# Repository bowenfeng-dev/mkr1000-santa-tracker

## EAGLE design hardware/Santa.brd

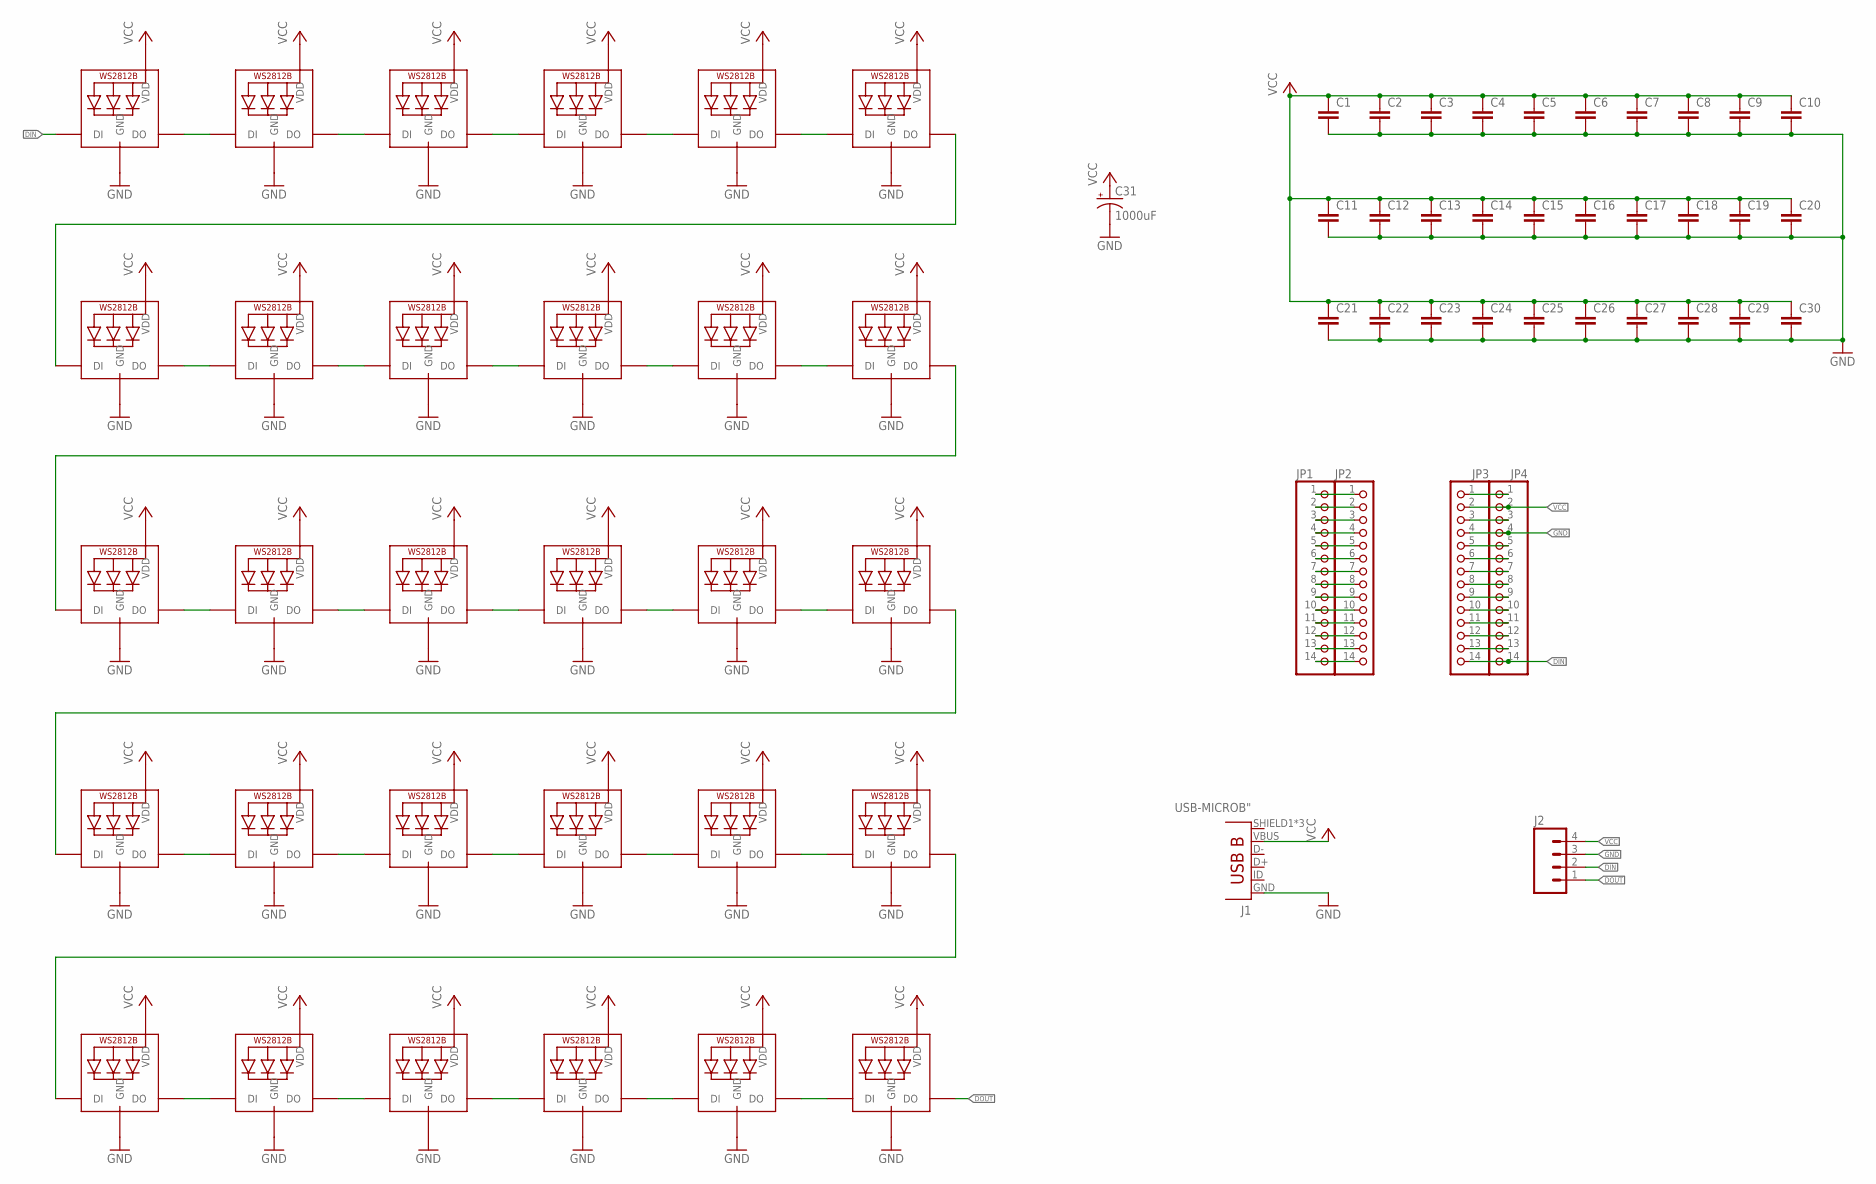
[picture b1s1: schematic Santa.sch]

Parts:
C1, C2, C3, C4, C5, C6, C7, C8, C9, C10, C11, C12, C13, C14, C15, C16, C17, C18, C19, C20, C21, C22, C23, C24, C25, C26, C27, C28, C29, C30: CC0603; C0603
C31: 1000uF; SMC_C
J1: USB-MICROB"; USB-B-MICRO-SMD_V03
J2: M04LOCK_LONGPADS; 1X04_LOCK_LONGPADS
JP1, JP2, JP3, JP4: PINHD-1X14-CB; 1X14-CB
LED1, LED2, LED3, LED4, LED5, LED6, LED7, LED8, LED9, LED10, LED11, LED12, LED13, LED14, LED15, LED16, LED17, LED18, LED19, LED20, LED21, LED22, LED23, LED24, LED25, LED26, LED27, LED28, LED29, LED30: WS2812B5050; WS2812B

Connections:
DIN: J2.2, JP3.14, JP4.14, LED1.4-DIN (DI)
DOUT: J2.1, LED30.2-DOUT (DO)
GND: C1.2, C2.2, C3.2, C4.2, C5.2, C6.2, C7.2, C8.2, C9.2, C10.2, C11.2, C12.2, C13.2, C14.2, C15.2, C16.2, C17.2, C18.2, C19.2, C20.2, C21.2, C22.2, C23.2, C24.2, C25.2, C26.2, C27.2, C28.2, C29.2, C30.2, C31.-, J1.GND, J2.3, JP3.4, JP4.4, LED1.3-GND (GND), LED2.3-GND (GND), LED3.3-GND (GND), LED4.3-GND (GND), LED5.3-GND (GND), LED6.3-GND (GND), LED7.3-GND (GND), LED8.3-GND (GND), LED9.3-GND (GND), LED10.3-GND (GND), LED11.3-GND (GND), LED12.3-GND (GND), LED13.3-GND (GND), LED14.3-GND (GND), LED15.3-GND (GND), LED16.3-GND (GND), LED17.3-GND (GND), LED18.3-GND (GND), LED19.3-GND (GND), LED20.3-GND (GND), LED21.3-GND (GND), LED22.3-GND (GND), LED23.3-GND (GND), LED24.3-GND (GND), LED25.3-GND (GND), LED26.3-GND (GND), LED27.3-GND (GND), LED28.3-GND (GND), LED29.3-GND (GND), LED30.3-GND (GND)
unnamed: LED1.2-DOUT (DO), LED2.4-DIN (DI)
unnamed: LED2.2-DOUT (DO), LED3.4-DIN (DI)
unnamed: LED3.2-DOUT (DO), LED4.4-DIN (DI)
unnamed: LED4.2-DOUT (DO), LED5.4-DIN (DI)
unnamed: LED5.2-DOUT (DO), LED6.4-DIN (DI)
unnamed: LED7.2-DOUT (DO), LED8.4-DIN (DI)
unnamed: LED8.2-DOUT (DO), LED9.4-DIN (DI)
unnamed: LED9.2-DOUT (DO), LED10.4-DIN (DI)
unnamed: LED10.2-DOUT (DO), LED11.4-DIN (DI)
unnamed: LED11.2-DOUT (DO), LED12.4-DIN (DI)
unnamed: LED13.2-DOUT (DO), LED14.4-DIN (DI)
unnamed: LED14.2-DOUT (DO), LED15.4-DIN (DI)
unnamed: LED15.2-DOUT (DO), LED16.4-DIN (DI)
unnamed: LED16.2-DOUT (DO), LED17.4-DIN (DI)
unnamed: LED17.2-DOUT (DO), LED18.4-DIN (DI)
unnamed: LED19.2-DOUT (DO), LED20.4-DIN (DI)
unnamed: LED20.2-DOUT (DO), LED21.4-DIN (DI)
unnamed: LED21.2-DOUT (DO), LED22.4-DIN (DI)
unnamed: LED22.2-DOUT (DO), LED23.4-DIN (DI)
unnamed: LED23.2-DOUT (DO), LED24.4-DIN (DI)
unnamed: LED25.2-DOUT (DO), LED26.4-DIN (DI)
unnamed: LED26.2-DOUT (DO), LED27.4-DIN (DI)
unnamed: LED27.2-DOUT (DO), LED28.4-DIN (DI)
unnamed: LED28.2-DOUT (DO), LED29.4-DIN (DI)
unnamed: LED29.2-DOUT (DO), LED30.4-DIN (DI)
unnamed: LED6.2-DOUT (DO), LED7.4-DIN (DI)
unnamed: LED12.2-DOUT (DO), LED13.4-DIN (DI)
unnamed: LED18.2-DOUT (DO), LED19.4-DIN (DI)
unnamed: LED24.2-DOUT (DO), LED25.4-DIN (DI)
unnamed: JP1.1, JP2.1
unnamed: JP1.2, JP2.2
unnamed: JP1.3, JP2.3
unnamed: JP1.4, JP2.4
unnamed: JP1.5, JP2.5
unnamed: JP1.6, JP2.6
unnamed: JP1.7, JP2.7
unnamed: JP1.8, JP2.8
unnamed: JP1.9, JP2.9
unnamed: JP1.10, JP2.10
unnamed: JP1.11, JP2.11
unnamed: JP1.12, JP2.12
unnamed: JP1.13, JP2.13
unnamed: JP1.14, JP2.14
unnamed: JP3.1, JP4.1
unnamed: JP3.3, JP4.3
unnamed: JP3.5, JP4.5
unnamed: JP3.6, JP4.6
unnamed: JP3.7, JP4.7
unnamed: JP3.8, JP4.8
unnamed: JP3.9, JP4.9
unnamed: JP3.10, JP4.10
unnamed: JP3.11, JP4.11
unnamed: JP3.12, JP4.12
unnamed: JP3.13, JP4.13
VCC: C1.1, C2.1, C3.1, C4.1, C5.1, C6.1, C7.1, C8.1, C9.1, C10.1, C11.1, C12.1, C13.1, C14.1, C15.1, C16.1, C17.1, C18.1, C19.1, C20.1, C21.1, C22.1, C23.1, C24.1, C25.1, C26.1, C27.1, C28.1, C29.1, C30.1, C31.+, J1.VBUS, J2.4, JP3.2, JP4.2, LED1.1-VDD (VDD), LED2.1-VDD (VDD), LED3.1-VDD (VDD), LED4.1-VDD (VDD), LED5.1-VDD (VDD), LED6.1-VDD (VDD), LED7.1-VDD (VDD), LED8.1-VDD (VDD), LED9.1-VDD (VDD), LED10.1-VDD (VDD), LED11.1-VDD (VDD), LED12.1-VDD (VDD), LED13.1-VDD (VDD), LED14.1-VDD (VDD), LED15.1-VDD (VDD), LED16.1-VDD (VDD), LED17.1-VDD (VDD), LED18.1-VDD (VDD), LED19.1-VDD (VDD), LED20.1-VDD (VDD), LED21.1-VDD (VDD), LED22.1-VDD (VDD), LED23.1-VDD (VDD), LED24.1-VDD (VDD), LED25.1-VDD (VDD), LED26.1-VDD (VDD), LED27.1-VDD (VDD), LED28.1-VDD (VDD), LED29.1-VDD (VDD), LED30.1-VDD (VDD)

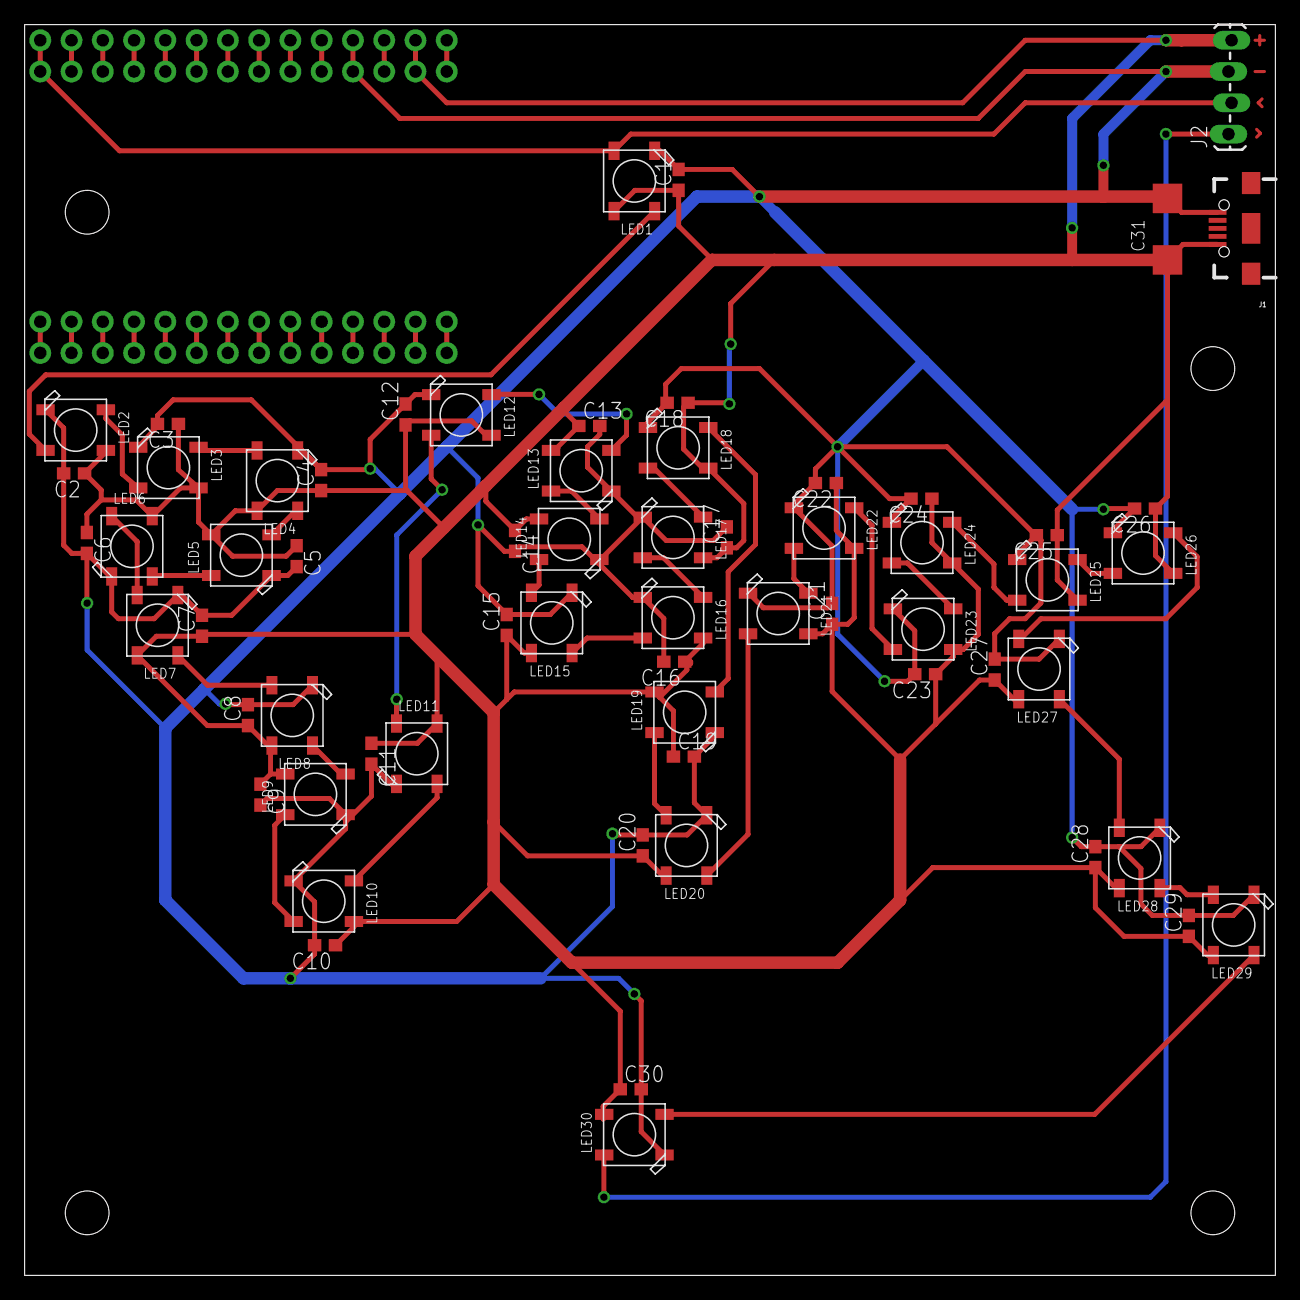
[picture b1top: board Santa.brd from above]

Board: 2 copper layers, 101.6 x 101.6 mm, 67 parts (0 on the bottom side), 58 nets.

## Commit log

2017-01-09 Parse locations from Google Santa API.
2017-01-09 Prints all LED locations.
2017-01-10 distance calculation
2017-01-10 sort by arrival
2017-01-10 inital flask fake server. fake time has not been implemented yet.
2017-01-10 fake clock is now working.
2017-01-11 Add auxiliary server to convert Santa response into a more microcontroller-friendly format.
2017-01-11 Add MKR1000 client. Just print response for now.
2017-01-12 Reduce generated json. from 23K+ -> 17K-
2017-01-12 Switch LEDs based on the response.
2017-01-22 restructure repo.
2017-01-22 Cleanup repo
2017-01-23 make it colorful

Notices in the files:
parts and their libraries:
SparkFun-Connectors: Licensing: Creative Commons ShareAlike 4.0 International - https://creativecommons.org/licenses/by-sa/4.0
